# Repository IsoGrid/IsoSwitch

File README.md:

# IsoSwitch.201802
IsoSwitch.201802 is a point-in-time release of the GPLv3-licensed source code and HW design for the CrowdSwitch product.
Please do not use the CrowdSwitch name for anything networking related. 
The CrowdSwitch name is claimed by Travis and Lindsey Martin.

# Status
This code is under active development; it's only being released to demonstrate our commitment to free/libre software. 
It's not ready for use as there are major missing features and missing tests. Please consider not judging the code quality until we declare a stable release :-)

This code is not yet useful as a switch: It only runs under an XMOS simulator.

# CrowdSwitch
<table>
 <tr>
  <td>
   
  </td>
  <td>
   
  </td>
 </tr>
</table>
CrowdSwitch is an open hardware product built using the [IsoGrid](http://www.isogrid.org) protocol. When wired together they form a streaming, scalable, mesh network.  
The full hardware design files (i.e. mechanical drawings, schematics, bill of materials, PCB layout data) are included in this release.

Our initial plan is to give low cost (or free) CrowdSwitches to low income residents of extremely 
high-density urban communities. 
The best funding model still isn't clear, but we intend to build it within a 501(c)(3) organization 
to make our altruistic motives super clear.
- 4-port auto-configuring switch
  - 3x RJ45 ~100 Mbps full-duplex [ethernet PHY](https://en.wikipedia.org/wiki/Ethernet_physical_layer#Fast_Ethernet) with 1ms worst-case switching latency
  - 1x RJ45 ~25 Mbps full-duplex Ethernet connection to an external controller PC or [SoC](https://en.wikipedia.org/wiki/System_on_a_chip) with 8ms worst-case switching latency 
- The core of the switch is an [xCORE-200 XL216-512-TQ128](http://www.xmos.com/download/private/xCORE-200-XL-Product-Brief%281.3%29.pdf)
- Powered by Micro USB
- Target BOM cost is ~$15.
- External controller PC/SoC (~$9) with ~512MB of RAM, ~16GB of flash, and able to create a wireless hotspot

The Wi-Fi on the PC/SoC will be able to work in one of two modes:
 1. Providing Internet access to a user
 2. Connecting to a regular Wi-Fi Internet access point

The IsoGrid formed by the interconnected mesh of CrowdSwitches provides a redundant multi-path backbone
to connect nodes operating in Mode (1) to nodes operating in Mode (2).

# Declaration & Dedication
    Copyright (2017-2018) Travis J Martin
    Copyright (2017) Lindsey A Martin
    
    IsoSwitch.201802 is free software: you can redistribute it and/or modify
    it under the terms of the GNU General Public License version 3 as published
    by the Free Software Foundation.

    IsoSwitch.201802 is distributed in the hope that it will be useful,
    but WITHOUT ANY WARRANTY; without even the implied warranty of
    MERCHANTABILITY or FITNESS FOR A PARTICULAR PURPOSE.  See the
    GNU General Public License version 3 for more details.

    You should have received a copy of the GNU General Public License version 3
    along with IsoSwitch.201802.  If not, see <http://www.gnu.org/licenses/>.

    A) We, the undersigned contributors to IsoSwitch.201802, declare that our 
       contribution was created by us as individuals, on our own time, entirely for 
       altruistic reasons, with the expectation and desire that the Copyright for our 
       contribution would expire in the year 2038 and enter the public domain.
    B) At the time when you first read this declaration, you are hereby granted a license
       to use IsoSwitch.201802 under the terms of the GNU General Public License, v3.
    C) Additionally, for all uses of IsoSwitch.201802 after Jan 1st 2038, we hereby waive 
       all copyright and related or neighboring rights together with all associated claims
       and causes of action with respect to this work to the extent possible under law.
    D) We have read and understand the terms and intended legal effect of CC0, and hereby 
       voluntarily elect to apply it to IsoSwitch.201802 for all uses or copies that occur 
       after Jan 1st 2038.
    E) To the extent that IsoSwitch.201802 embodies any of our patentable inventions, we 
       hearby grant you a worldwide, royalty-free, non-exclusive, perpetual license to 
       those inventions.

|    Signature     |  Declarations   |                                                     Acknowledgments                                                                                      |
|:----------------:|:---------------:|:--------------------------------------------------------------------------------------------------------------------------------------------------------:|
| Travis J Martin  |    A,B,C,D,E    | My loving wife, Lindsey Ann Irwin Martin, for her incredible support on our journey!                                   |
| Lindsey A Martin |    A,B,C,D,E    | Travis' spirit of thinking big, desire to help humanity, and much hard work that has made this project a reality.            |

# Contribution Policy
Join our [Slack team](https://crowdswitch.slack.com) and ask us for ways you can help. 
Those of us working on the CrowdSwitch Project are only trying to do good; contributions that don't 
further the goals of the CrowdSwitch Project will be rejected. Non-trivial contributions should include 
the CrowdSwitch copyright/license declaration signed by the contributor. We'll consider pull requests 
without the declaration if the contribution is small enough to obviously avoid copyright/patent concerns. 
If you don't like the declaration, let us know why; perhaps we can work something out. Otherwise, feel 
free to fork it under the terms of the GPLv3 license.

# Details
| Component         | Description                                                                         |
|-------------------|-------------------------------------------------------------------------------------|
| HMLM(Test)        | Prototype HashMatchLogMap route mapping algorithm                                   |
| HW                | Schematic, PCB Layout in KiCad format. BoM in xlsx format                           |
| HW\Datasheets     | Archived datasheets for select components                                           |
| HW\SnapEda        | Symbols and Footprints for some components, freely licensed by SnapEda              |
| IsoSwitch         | C# implementation of an IsoGrid switch controller (bridging C# interfaces and ETH)  |
| XMOS\             |                                                                                     |
| XMOS\EthPluginX   | Simulation plugin for Ethernet PHY in XMOS\IsoSwitch using named-pipes              |
| XMOS\IsoSwitch    | 16-core XMOS Firmware implementing the High-performance kernel of an IsoGrid switch |

# Build and Test
### Common Instructions for Windows:
* Install Visual Studio Community 2017 (C/C++) from [here](https://www.visualstudio.com/downloads/)
* Install XMOS's [xTIMEcomposer Studio 14.3.2](https://www.xmos.com/published/xtimecomposer-community_14-microsoft-installer?ver=latest)
* Open xTIMEcomposer and open the Workspace at \XMOS
* Build the \XMOS\IsoSwitch project in xTIMEcomposer
* Open the CrowdSwitch.sln in Visual Studio
* Rebuild the solution

### Simulator-Only Test
* Run IsoSwitchTest.UT1.SimpleStream from Test Explorer
  * It runs for 7-9 minutes

### XCore-200 SliceKIT (proof-of-concept test)
* You'll need an [XCORE-200 SliceKIT](https://www.xmos.com/support/boards?product=35833)
* You'll need 3x [Ethernet | XA-SK-E100 SliceCARDs](https://www.xmos.com/support/boards?product=15830)
* Plug the Ethernet SliceCARDs into Tile-1-Star, Tile-1-Triangle, and Tile-0-Triangle
* Connect a crossover Ethernet cable between Tile-1-Triangle and Tile-0-Triangle
* Connect an Ethernet cable between Tile-1-Star and your test PC
* Build and install the ndisprot driver fork at: https://github.com/IsoGrid/NdisProtocol
* Enable the IsoSwitch NDIS Protocol driver only on the one Ethernet port on your PC
* run "net start ndisprot" from an elevated command prompt
* Run IsoSwitchTest.UT1.SliceKitBringupTest from Test Explorer in the CrowdSwitch Visual Studio solution
  * It runs for 30 seconds

# LICENSES
GPLv3: <http://www.gnu.org/licenses/>
* IsoSwitch.201802

Apache 2.0: http://www.apache.org/licenses/LICENSE-2.0
* DamienG.Security.Cryptography

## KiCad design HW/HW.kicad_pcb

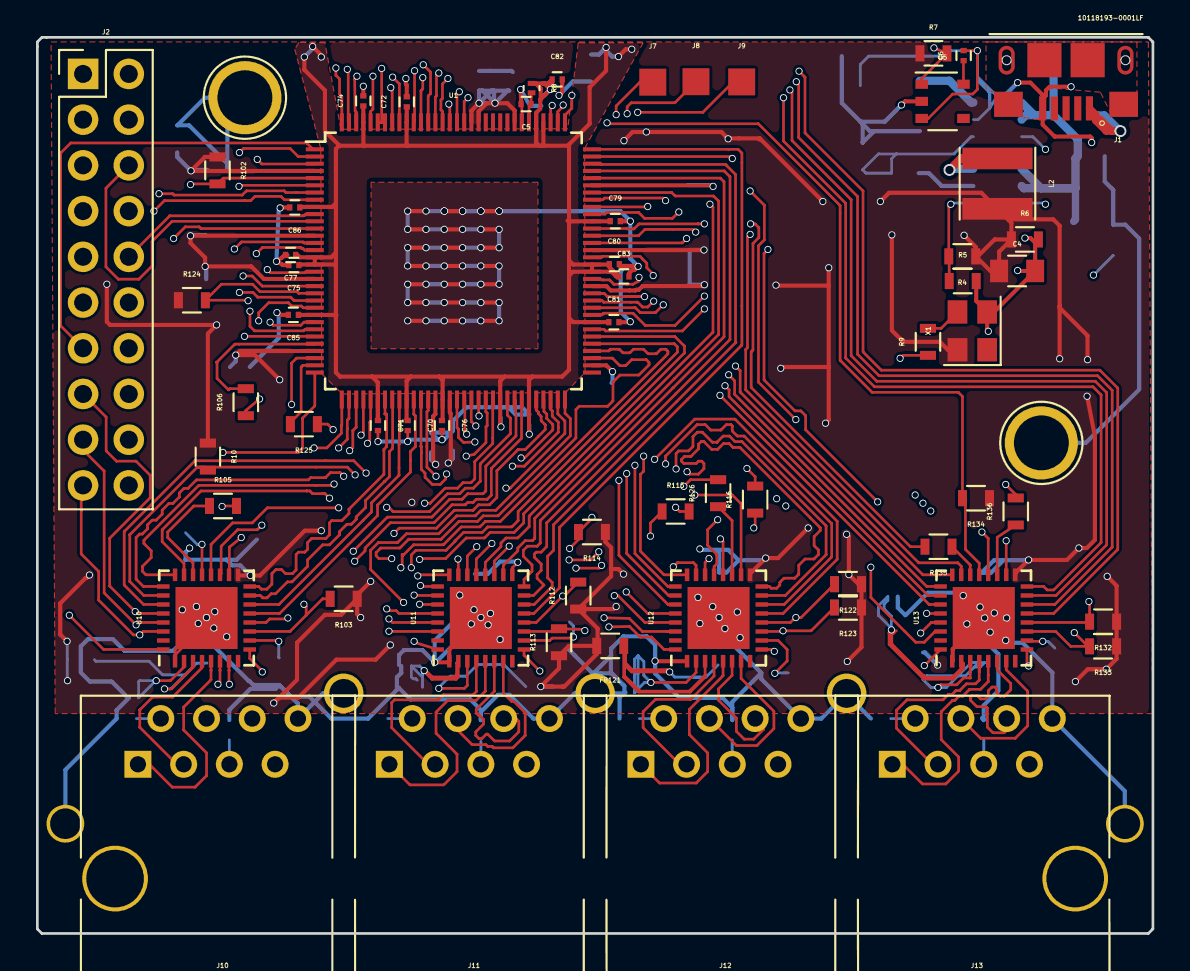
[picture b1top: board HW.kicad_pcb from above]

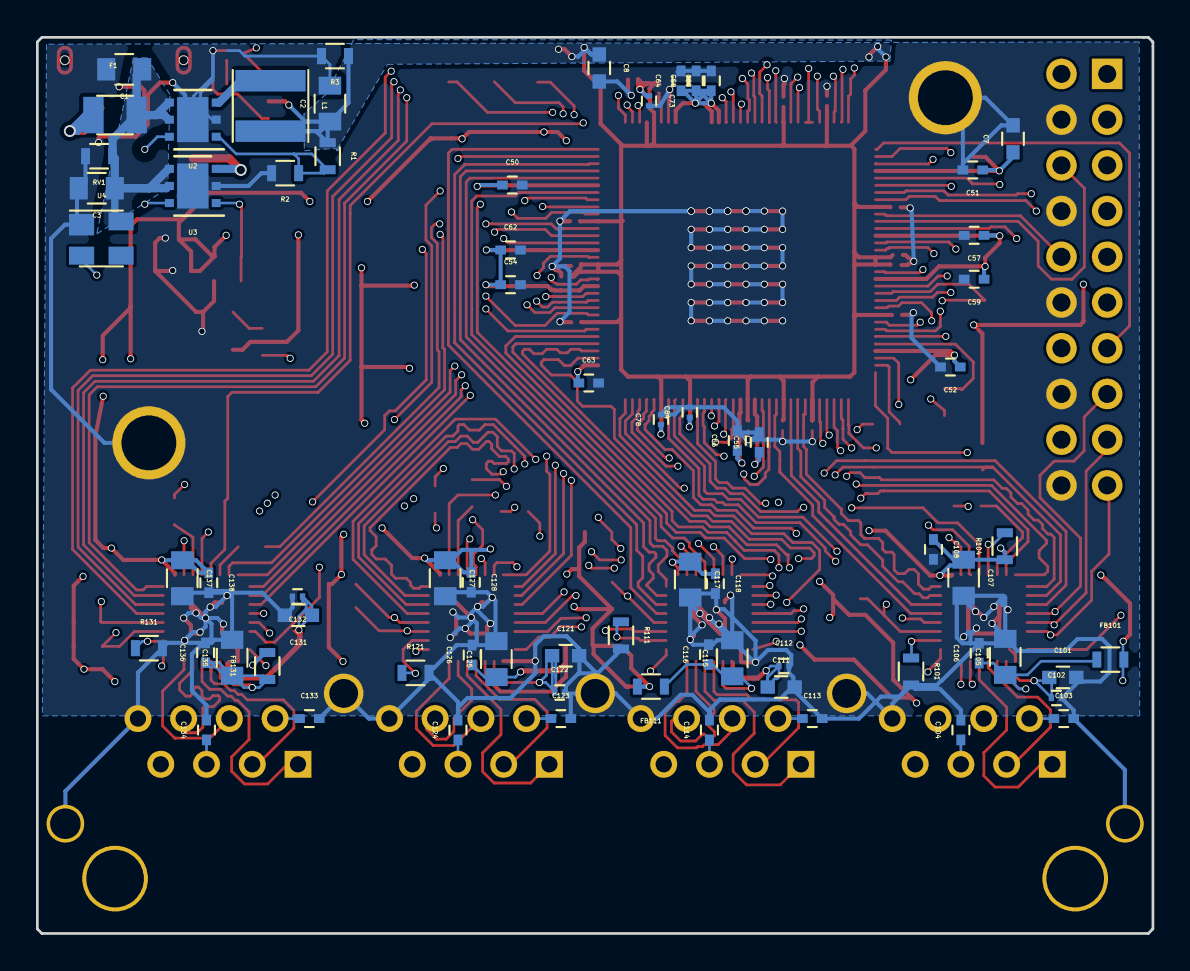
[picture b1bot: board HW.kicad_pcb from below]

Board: 4 copper layers, 62.0 x 49.8 mm, 133 parts (70 on the bottom side), 147 nets.

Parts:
C1, C3: 4.7uF; C_0805
C2, C4, C105, C107, C115, C117, C125, C127, C135, C137: 22uF; C_0805
C5, C6, C70, C71, C72, C73, C74, C75, C76, C77, C78, C79, C80, C81, C82, C83, C84, C85, C86, C102, C112, C122, C132: 100nF; C_0201
C7, C8, C101, C111, C121, C131: 2.2uF; C_0603
C50, C51, C52, C53, C54, C55, C56, C57, C58, C59, C62, C63, C64, C103, C104, C106, C108, C113, C114, C116, C118, C123, C124, C126, C128, C133, C134, C136, C138: 100nF; C_0402
F1: 1206L110; Fuse_SMD1206_Reflow
FB101, FB111, FB121, FB131: FERRITE BEAD; L_0603
J1: 10118193-0001LF; FCI_10118193-0001LF
J2: 2x10 Vertical Pin; Pin_Header_Straight_2x10_Pitch2.54mm
J7: NWAY_TP; Measurement_Point_Square-SMD-Pad_Small
J8: CRS_TP; Measurement_Point_Square-SMD-Pad_Small
J9: COL_TP; Measurement_Point_Square-SMD-Pad_Small
J10, J11, J12, J13: RJ45_0; RJ45_LINK-PP
L1, L2: 3.3uH; L_Taiyo-Yuden_NR-40xx
Mount2, Mount3: 1pin
R1: 4.7K; R_0603
R2, R4: 18K; R_0603
R3, R103, R104, R113, R114, R123, R124, R133, R134: 1K; R_0603
R5: 5.6K; R_0603
R6: 2.2K; R_0603
R7: 47K; R_0603
R8: 4.7R; R_0201
R9, R105, R106, R115, R116, R125, R126, R135, R136: 33R; R_0603
R10: 3.3K; R_0603
R101, R111, R121, R131: 6.49K; R_0603
R102, R112, R122, R132: 10K; R_0603
RV1: V5.5MLA0603H; R_0603
U1: XL216-512-TQ128_CHIP_VIEW; TQFP-128_14x14mm_Pitch0.4mm
U2, U3: ST1S06; DFN6D_3x3mm
U4: APX811-46UG-7; SOT-143
U5: NCP303LSN10T; TSOP-5_1.65x3.05mm_Pitch0.95mm
U10, U11, U12, U13: KSZ8081MNX; QFN-32-1EP_5x5mm_Pitch0.5mm
X1: DSC6001CI2A-025.0000; Oscillator_SMD_Abracon_ASE-4pin_3.2x2.5mm

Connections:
25M: R9.1, U1.124, U10.9, U11.9, U12.9, U13.9
+1V0: C2.1, C8.1, C70.1, C71.1, C72.1, C73.1, C74.1, C75.1, C76.1, C77.1, C78.1, C79.1, C80.1, C81.1, C82.1, C83.1, C84.1, C85.1, C86.1, L1.2, R1.1, R3.1, R8.1, U1.9, U1.16, U1.17, U1.24, U1.38, U1.42, U1.47, U1.55, U1.59, U1.72, U1.79, U1.80, U1.86, U1.100, U1.101, U1.119, U1.125, U5.2
+3V3: C4.1, C7.1, C50.1, C51.1, C52.1, C53.1, C54.1, C55.1, C56.1, C57.1, C58.1, C59.1, C62.1, C63.1, C64.1, C107.1, C108.1, C117.1, C118.1, C127.1, C128.1, C137.1, C138.1, FB101.2, FB111.2, FB121.2, FB131.2, L2.2, R4.1, R6.1, R7.1, R10.1, R102.1, R103.1, R104.1, R112.1, R113.1, R114.1, R122.1, R123.1, R124.1, R132.1, R133.1, R134.1, U1.4, U1.13, U1.19, U1.29, U1.46, U1.48, U1.66, U1.77, U1.82, U1.91, U1.104, U1.109, U1.110, U10.17, U11.17, U12.17, U13.17, X1.4
+5V: C1.1, C3.1, F1.2, RV1.1, U2.4, U2.5, U3.4, U3.5, U4.4
/PG_5V: U2.6, U3.6, U4.2
/Tile0/EthernetPort0/INT: R104.2, U1.6, U10.21
/Tile0/EthernetPort0/MDC: R102.2, U1.5, U10.12
/Tile0/EthernetPort0/MDIO: R103.2, U1.3, U10.11
/Tile0/EthernetPort0/RST_N: U1.2, U10.32
/Tile0/EthernetPort0/RXC: R106.2, U1.28
/Tile0/EthernetPort0/RXD0: U1.39, U10.16
/Tile0/EthernetPort0/RXD1: U1.40, U10.15
/Tile0/EthernetPort0/RXD2: U1.41, U10.14
/Tile0/EthernetPort0/RXD3: U1.43, U10.13
/Tile0/EthernetPort0/RXDV: U1.27, U10.18
/Tile0/EthernetPort0/RXERR: U1.56, U10.20
/Tile0/EthernetPort0/TXC: R105.2, U1.32
/Tile0/EthernetPort0/TXD0: U1.34, U10.24
/Tile0/EthernetPort0/TXD1: U1.35, U10.25
/Tile0/EthernetPort0/TXD2: R10.2, U1.36, U10.26
/Tile0/EthernetPort0/TXD3: U1.37, U10.27
/Tile0/EthernetPort0/TXEN: U1.33, U10.23
/Tile0/EthernetPort1/COL: J9.1, U1.97, U11.28
/Tile0/EthernetPort1/CRS: J8.1, U1.98, U11.29
/Tile0/EthernetPort1/INT: R114.2, U1.63, U11.21
/Tile0/EthernetPort1/MDC: R112.2, U1.87, U11.12
/Tile0/EthernetPort1/MDIO: R113.2, U1.88, U11.11
/Tile0/EthernetPort1/NWAYEN: J7.1, U1.99, U11.30
/Tile0/EthernetPort1/RST_N: U1.64, U11.32
/Tile0/EthernetPort1/RXC: R116.2, U1.89
/Tile0/EthernetPort1/RXD0: U1.92, U11.16
/Tile0/EthernetPort1/RXD1: U1.93, U11.15
/Tile0/EthernetPort1/RXD2: U1.94, U11.14
/Tile0/EthernetPort1/RXD3: U1.96, U11.13
/Tile0/EthernetPort1/RXDV: U1.90, U11.18
/Tile0/EthernetPort1/RXERR: U1.95, U11.20
/Tile0/EthernetPort1/TXC: R115.2, U1.62
/Tile0/EthernetPort1/TXD0: U1.67, U11.24
/Tile0/EthernetPort1/TXD1: U1.68, U11.25
/Tile0/EthernetPort1/TXD2: U1.69, U11.26
/Tile0/EthernetPort1/TXD3: U1.70, U11.27
/Tile0/EthernetPort1/TXEN: U1.61, U11.23
/Tile1/EthernetPort2/COL: U1.25, U12.28
/Tile1/EthernetPort2/CRS: U1.23, U12.29
/Tile1/EthernetPort2/INT: R124.2, U1.21, U12.21
/Tile1/EthernetPort2/MDC: R122.2, U1.53, U12.12
/Tile1/EthernetPort2/MDIO: R123.2, U1.54, U12.11
/Tile1/EthernetPort2/NWAYEN: U1.22, U12.30
/Tile1/EthernetPort2/RST_N: U1.20, U12.32
/Tile1/EthernetPort2/RXC: R126.2, U1.44
/Tile1/EthernetPort2/RXD0: U1.49, U12.16
/Tile1/EthernetPort2/RXD1: U1.50, U12.15
/Tile1/EthernetPort2/RXD2: U1.51, U12.14
/Tile1/EthernetPort2/RXD3: U1.52, U12.13
/Tile1/EthernetPort2/RXDV: U1.45, U12.18
/Tile1/EthernetPort2/RXERR: U1.26, U12.20
/Tile1/EthernetPort2/TXC: R125.2, U1.31
/Tile1/EthernetPort2/TXD0: U1.111, U12.24
/Tile1/EthernetPort2/TXD1: U1.112, U12.25
/Tile1/EthernetPort2/TXD2: U1.117, U12.26
/Tile1/EthernetPort2/TXD3: U1.118, U12.27
/Tile1/EthernetPort2/TXEN: U1.30, U12.23
/Tile1/EthernetPort3/COL: U1.73, U13.28
/Tile1/EthernetPort3/CRS: U1.81, U13.29
/Tile1/EthernetPort3/INT: R134.2, U1.12, U13.21
/Tile1/EthernetPort3/MDC: R132.2, U1.14, U13.12
/Tile1/EthernetPort3/MDIO: R133.2, U1.15, U13.11
/Tile1/EthernetPort3/NWAYEN: U1.83, U13.30
/Tile1/EthernetPort3/RST_N: U1.18, U13.32
/Tile1/EthernetPort3/RXC: R136.2, U1.120
/Tile1/EthernetPort3/RXD0: U1.113, U13.16
/Tile1/EthernetPort3/RXD1: U1.114, U13.15
/Tile1/EthernetPort3/RXD2: U1.115, U13.14
/Tile1/EthernetPort3/RXD3: U1.116, U13.13
/Tile1/EthernetPort3/RXDV: U1.121, U13.18
/Tile1/EthernetPort3/RXERR: U1.71, U13.20
/Tile1/EthernetPort3/TXC: R135.2, U1.85
/Tile1/EthernetPort3/TXD0: U1.74, U13.24
/Tile1/EthernetPort3/TXD1: U1.75, U13.25
/Tile1/EthernetPort3/TXD2: U1.76, U13.26
/Tile1/EthernetPort3/TXD3: U1.78, U13.27
/Tile1/EthernetPort3/TXEN: U1.84, U13.23
COL0: J2.15, U1.57, U10.28
CRS0: J2.17, U1.58, U10.29
GND: C1.2, C2.2, C3.2, C4.2, C5.2, C6.2, C7.2, C8.2, C50.2, C51.2, C52.2, C53.2, C54.2, C55.2, C56.2, C57.2, C58.2, C59.2, C62.2, C63.2, C64.2, C70.2, C71.2, C72.2, C73.2, C74.2, C75.2, C76.2, C77.2, C78.2, C79.2, C80.2, C81.2, C82.2, C83.2, C84.2, C85.2, C86.2, C101.2, C102.2, C103.2, C104.2, C105.2, C106.2, C107.2, C108.2, C111.2, C112.2, C113.2, C114.2, C115.2, C116.2, C117.2, C118.2, C121.2, C122.2, C123.2, C124.2, C125.2, C126.2, C127.2, C128.2, C131.2, C132.2, C133.2, C134.2, C135.2, C136.2, C137.2, C138.2, J1.5, J2.4, J2.8, J2.12, J2.16, J2.20, J10.8, J10.9, J10.10, J11.8, J11.10, J12.8, J12.10, J13.8, J13.11, Mount2.1, Mount3.1, R2.2, R3.2, R5.2, R6.2, R101.2, R111.2, R121.2, R131.2, RV1.2, U1.103, U2.2, U2.7, U3.2, U3.7, U4.1, U5.3, U10.1, U10.33, U11.1, U11.33, U12.1, U12.33, U13.1, U13.33, X1.2
NWAYEN0: J2.19, U1.60, U10.30
unnamed: C5.1, R8.2, U1.102
unnamed: C6.1, U5.6
unnamed: C101.1, C102.1, U10.2
unnamed: C103.1, J10.2
unnamed: C104.1, J10.5
unnamed: C105.1, C106.1, FB101.1, U10.3
unnamed: C111.1, C112.1, U11.2
unnamed: C113.1, J11.2
unnamed: C114.1, J11.5
unnamed: C115.1, C116.1, FB111.1, U11.3
unnamed: C121.1, C122.1, U12.2
unnamed: C123.1, J12.2
unnamed: C124.1, J12.5
unnamed: C125.1, C126.1, FB121.1, U12.3
unnamed: C131.1, C132.1, U13.2
unnamed: C133.1, J13.2
unnamed: C134.1, J13.5
unnamed: C135.1, C136.1, FB131.1, U13.3
unnamed: F1.1, J1.1
unnamed: J2.5, U1.128
unnamed: J2.6, U1.11
unnamed: J2.7, U1.126
unnamed: J2.9, U1.127
unnamed: J2.10, U1.10
unnamed: J2.13, U1.1
unnamed: J2.14, U1.8
unnamed: J2.18, U1.7
unnamed: J10.1, U10.5
unnamed: J10.3, U10.4
unnamed: J10.4, U10.7
unnamed: J10.6, U10.6
unnamed: J11.1, U11.5
unnamed: J11.3, U11.4
unnamed: J11.4, U11.7
unnamed: J11.6, U11.6
unnamed: J12.1, U12.5
unnamed: J12.3, U12.4
unnamed: J12.4, U12.7
unnamed: J12.6, U12.6
unnamed: J13.1, U13.5
unnamed: J13.3, U13.4
unnamed: J13.4, U13.7
unnamed: J13.6, U13.6
unnamed: L1.1, U2.3
unnamed: L2.1, U3.3
unnamed: R1.2, R2.1, U2.1
unnamed: R4.2, R5.1, U3.1
unnamed: R7.2, U1.122, U1.123, U5.1
unnamed: R9.2, X1.3
unnamed: R101.1, U10.10
unnamed: R105.1, U10.22
unnamed: R106.1, U10.19
unnamed: R111.1, U11.10
unnamed: R115.1, U11.22
unnamed: R116.1, U11.19
unnamed: R121.1, U12.10
unnamed: R125.1, U12.22
unnamed: R126.1, U12.19
unnamed: R131.1, U13.10
unnamed: R135.1, U13.22
unnamed: R136.1, U13.19

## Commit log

2017-09-19 Releasing IsoSwitch.201709
2017-09-20 Fix misspelling of name in copyright
2017-09-20 Attempting to fix formatting
2017-09-20 Again, trying to fix formatting.
2017-09-20 Fixed formatting
2018-01-06 Releasing IsoSwitch.201801
2018-01-06 Fixing Image links
2018-01-06 Fix image formatting
2018-03-01 Releasing IsoSwitch.201802
